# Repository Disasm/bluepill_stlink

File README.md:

# bluepill_stlink
A shield for a Blue Pill board to act as ST-LINK/DAPLink probe

## Building the firmware

    git clone https://github.com/Disasm/dap42.git
    git checkout bluepill-shield
    make DAP103-BLUEPILL-SHIELD.bin

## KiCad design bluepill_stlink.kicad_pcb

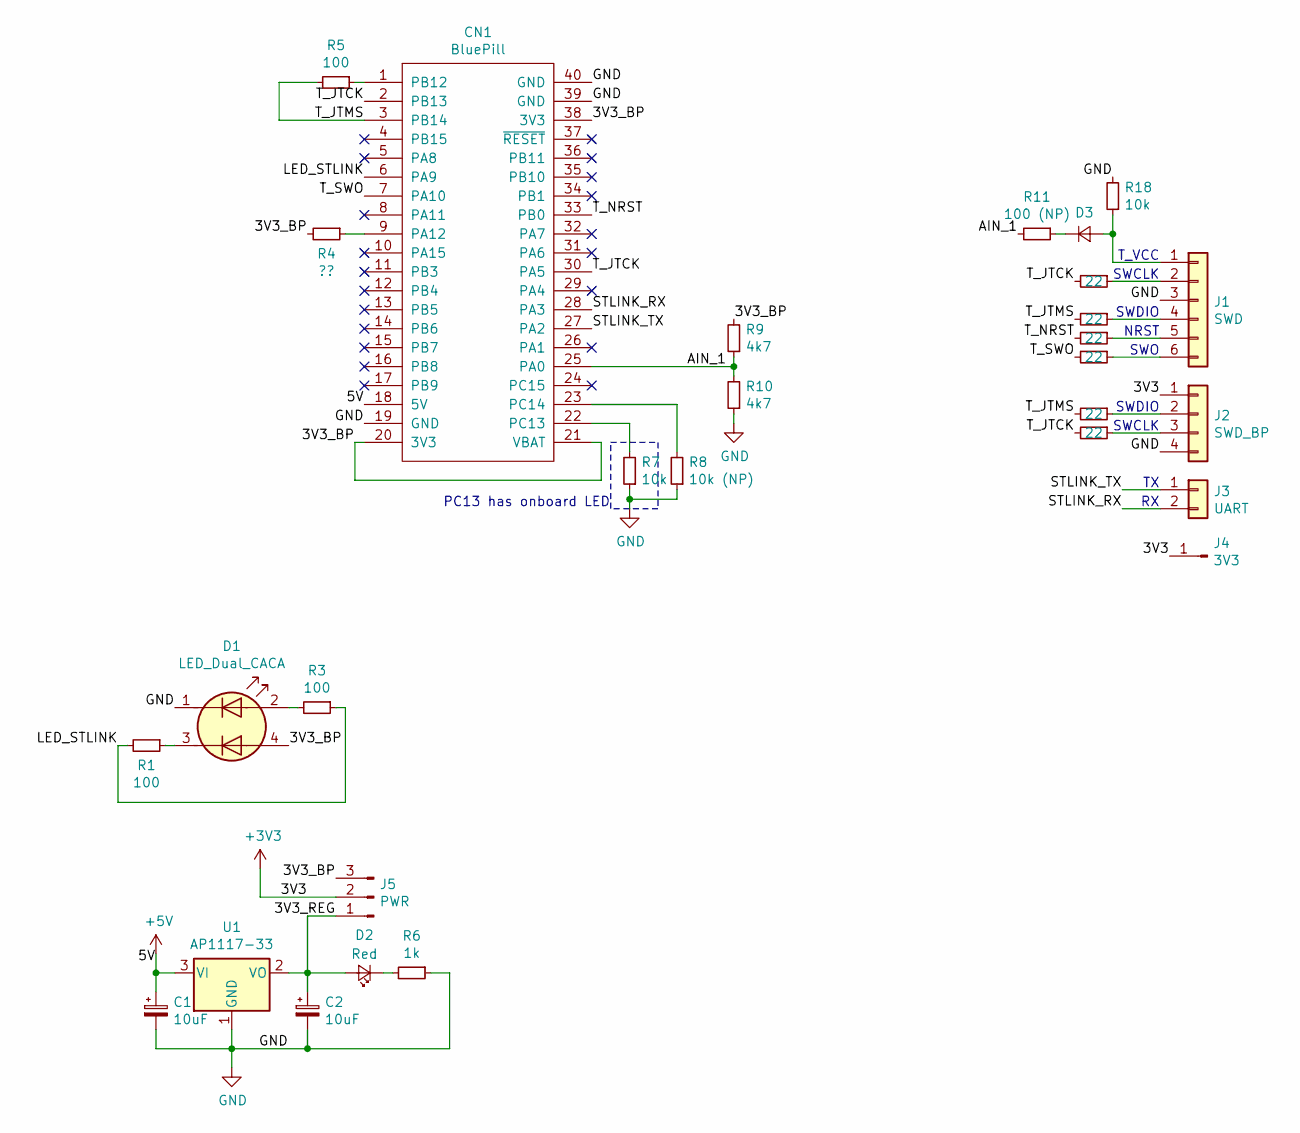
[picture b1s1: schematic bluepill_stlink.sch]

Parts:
C1, C2: 10uF; CP_EIA-3216-18_Kemet-A
CN1: BluePill
D1: LED_Dual_CACA; LED_Kingbright_AAA3528ESGCT
D2: Red; LED_1206_3216Metric
D3: D_Small; D_1206_3216Metric
J1: SWD; PinHeader_1x06_P2.54mm_Vertical
J2: SWD_BP; PinSocket_1x04_P2.54mm_Horizontal_Mirrored
J3: UART; PinHeader_1x02_P2.54mm_Vertical
J4: 3V3; SolderWirePad_1x01_Drill0.8mm
J5: PWR; PinHeader_1x03_P2.54mm_Vertical
R1, R3, R5: 100; R_1206_3216Metric
R4: ??; R_1206_3216Metric
R6: 1k; R_1206_3216Metric
R7, R18: 10k; R_1206_3216Metric
R8: 10k (NP); R_1206_3216Metric
R9, R10: 4k7; R_1206_3216Metric
R11: 100 (NP); R_1206_3216Metric
R12, R13, R14, R15, R16, R17: 22; R_1206_3216Metric
U1: AP1117-33; SOT-223-3_TabPin2

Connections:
+3V3: J2.1, J4.1, J5.2
+5V: C1.1, CN1.18 (5V), U1.3 (VI)
/3V3_BP: CN1.20 (3V3), CN1.21 (VBAT), CN1.38 (3V3), D1.4 (K2), J5.3, R4.2, R9.2
/3V3_REG: C2.1, D2.2 (A), J5.1, U1.2 (VO)
/AIN_1: CN1.25 (PA0), R9.1, R10.2, R11.2
/LED_STLINK: CN1.6 (PA9), R1.2, R3.1
/STLINK_RX: CN1.28 (PA3), J3.2
/STLINK_TX: CN1.27 (PA2), J3.1
/T_JTCK: CN1.2 (PB13), CN1.30 (PA5), R12.2, R17.2
/T_JTMS: CN1.3 (PB14), R5.2, R13.2, R16.2
/T_NRST: CN1.33 (PB0), R14.2
/T_SWO: CN1.7 (PA10), R15.2
GND: C1.2, C2.2, CN1.19 (GND), CN1.39 (GND), CN1.40 (GND), D1.1 (A1), J1.3, J2.4, R6.1, R7.1, R8.1, R10.1, R18.2, U1.1 (GND)
unnamed: CN1.1 (PB12), R5.1
unnamed: CN1.9 (PA12), R4.1
unnamed: CN1.22 (PC13), R7.2
unnamed: CN1.23 (PC14), R8.2
unnamed: D1.2 (K1), R3.2
unnamed: D1.3 (A2), R1.1
unnamed: D2.1 (K), R6.2
unnamed: D3.1 (K), R11.1
unnamed: D3.2 (A), J1.1, R18.1
unnamed: J1.2, R12.1
unnamed: J1.4, R13.1
unnamed: J1.5, R14.1
unnamed: J1.6, R15.1
unnamed: J2.2, R16.1
unnamed: J2.3, R17.1

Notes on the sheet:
SWDIO
SWCLK
NRST
SWO
T_VCC
PC13 has onboard LED

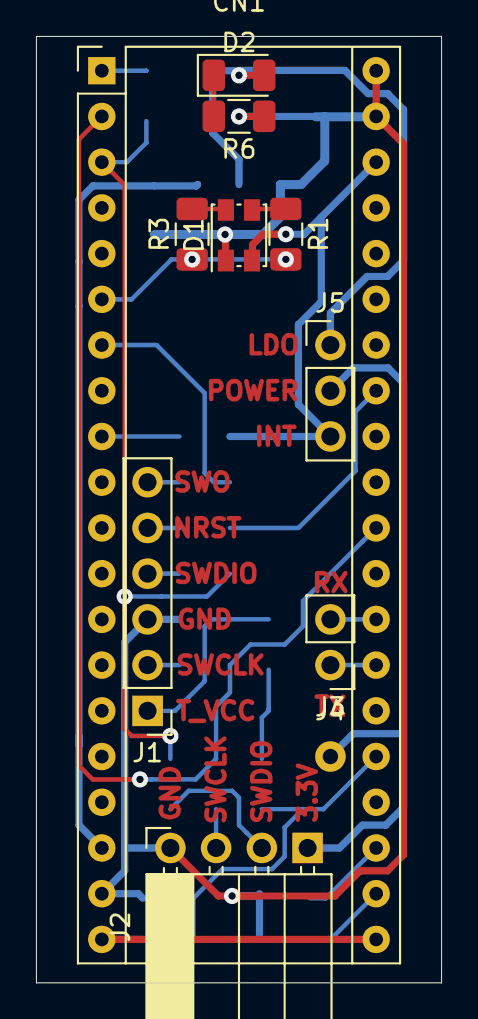
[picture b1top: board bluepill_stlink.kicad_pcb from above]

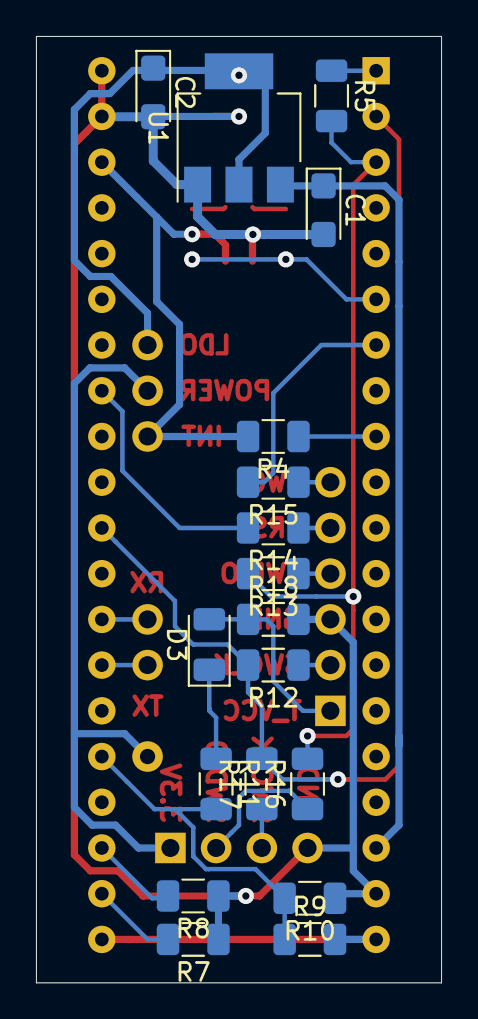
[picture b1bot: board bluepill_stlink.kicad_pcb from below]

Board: 2 copper layers, 22.5 x 52.6 mm, 29 parts (18 on the bottom side), 28 nets.

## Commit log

2020-03-11 Add kicad_libs submodule
2020-03-11 Add KiCad project files
2020-03-11 Add Gerber files
2020-03-11 Add BOM
2020-03-11 Add README.md
